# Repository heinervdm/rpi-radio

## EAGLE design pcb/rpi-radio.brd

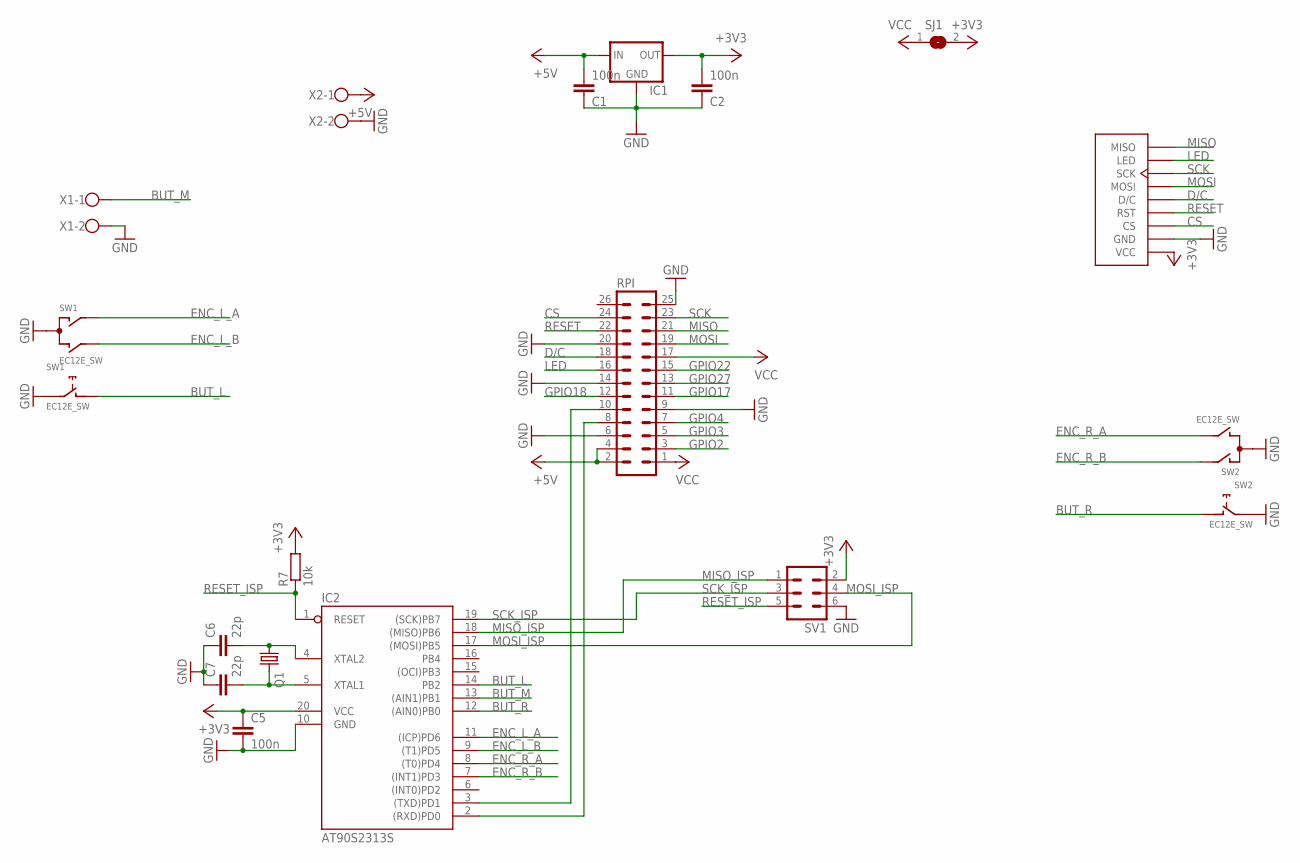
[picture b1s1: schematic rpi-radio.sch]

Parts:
C1, C2, C5: 100n; C0805
C6, C7: 22p; C0805
IC1: 78XXS
IC2: AT90S2313S; SO20L
Q1: CRYSTALHC49S; HC49/S
R7: 10k; M0805
RPI: ML26
SJ1: SJ
SV1: ML6
SW1, SW2: EC12E_SW; ALPS_EC12E_SW
U$4: DISPLAY
X1, X2: W237-102

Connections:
+3V3: C2.2, C5.1, IC1.OUT, IC2.20 (VCC), R7.2, SJ1.2, SV1.2, U$4.P$1 (VCC)
+5V: C1.2, IC1.IN, RPI.2, RPI.4, X2.1
BUT_L: IC2.14 (PB2), SW1.D (1)
BUT_M: IC2.13 ((AIN1)PB1), X1.1
BUT_R: IC2.12 ((AIN0)PB0), SW2.D (1)
CS: RPI.24, U$4.P$3 (CS)
D/C: RPI.18, U$4.P$5 (D/C)
ENC_L_A: IC2.11 ((ICP)PD6), SW1.A
ENC_L_B: IC2.9 ((T1)PD5), SW1.B
ENC_R_A: IC2.8 ((T0)PD4), SW2.B
ENC_R_B: IC2.7 ((INT1)PD3), SW2.A
GND: C1.1, C2.1, C5.2, C6.1, C7.1, IC1.GND, IC2.10 (GND), RPI.6, RPI.9, RPI.14, RPI.20, RPI.25, SV1.6, SW1.C, SW1.E (2), SW2.C, SW2.E (2), U$4.P$2 (GND), X1.2, X2.2
GPIO2: RPI.3
GPIO3: RPI.5
GPIO4: RPI.7
GPIO17: RPI.11
GPIO18: RPI.12
GPIO22: RPI.15
GPIO27: RPI.13
LED: RPI.16, U$4.P$8 (LED)
MISO: RPI.21, U$4.P$9 (MISO)
MISO_ISP: IC2.18 ((MISO)PB6), SV1.1
MOSI: RPI.19, U$4.P$6 (MOSI)
MOSI_ISP: IC2.17 ((MOSI)PB5), SV1.4
unnamed: C6.2, IC2.4 (XTAL2), Q1.1
unnamed: IC2.2 ((RXD)PD0), RPI.8
unnamed: IC2.3 ((TXD)PD1), RPI.10
unnamed: C7.2, IC2.5 (XTAL1), Q1.2
RESET: RPI.22, U$4.P$4 (RST)
RESET_ISP: IC2.1 (RESET), R7.1, SV1.5
SCK: RPI.23, U$4.P$7 (SCK)
SCK_ISP: IC2.19 ((SCK)PB7), SV1.3
VCC: RPI.1, RPI.17, SJ1.1

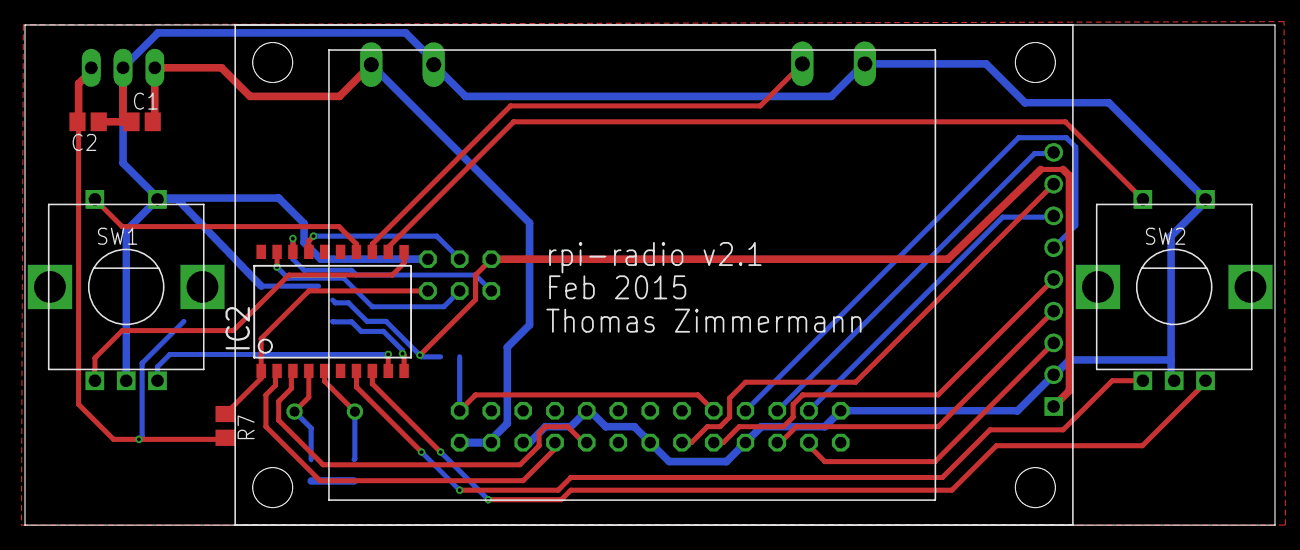
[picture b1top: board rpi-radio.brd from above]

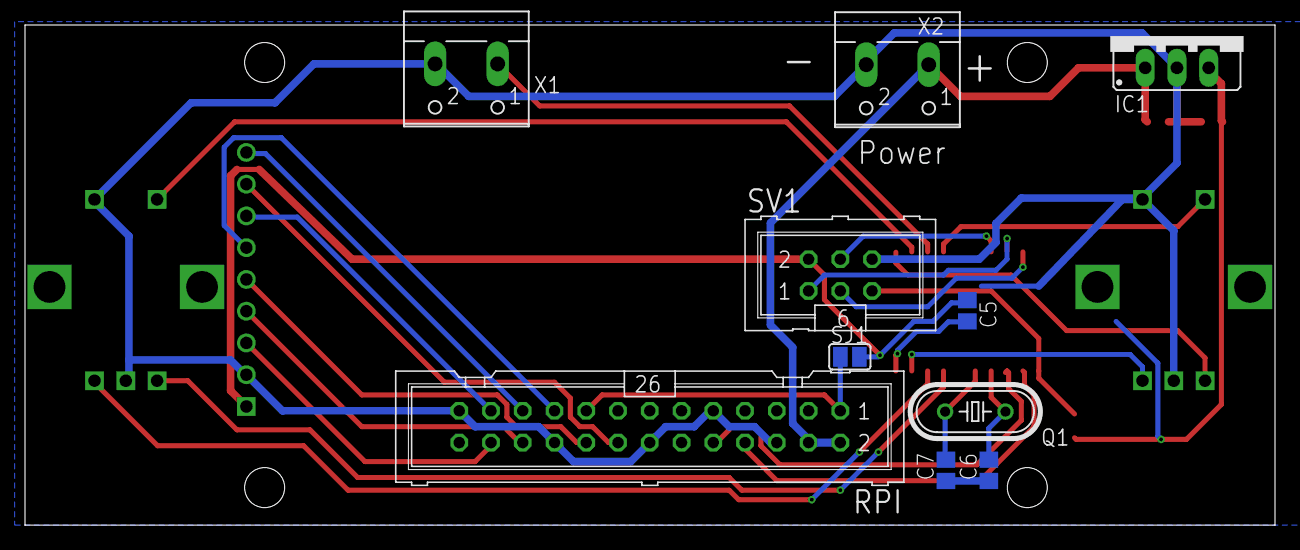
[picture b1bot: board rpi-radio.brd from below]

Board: 2 copper layers, 100.0 x 40.0 mm, 17 parts (10 on the bottom side), 26 nets.

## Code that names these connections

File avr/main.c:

/*
 * Debounce routine by Peter Dannegger: https://www.mikrocontroller.net/articles/Entprellung#Timer-Verfahren_.28nach_Peter_Dannegger.29
 * 
 * Rotary encoder routine by Peter Dannegger: https://www.mikrocontroller.net/articles/Drehgeber#Solide_L.C3.B6sung:_Beispielcode_in_C
 * 
 * UART lib by Peter Fleury: http://homepage.hispeed.ch/peterfleury/avr-software.html#libs
 */

#include <avr/interrupt.h>
#include <avr/io.h>
#include <stdlib.h>

#include "lib/uartlibrary/uart.h"

#ifndef F_CPU
#define F_CPU 14745600UL
#endif

#define UART_BAUD_RATE 9600

#define ENC_PIN    PIND
#define ENC_PORT   PORTD
#define ENC_DDR    DDRD
#define ENC0A_P    PD3
#define ENC0B_P    PD4
#define ENC1A_P    PD5
#define ENC1B_P    PD6

#define PHASE_0A     (ENC_PIN & 1<<ENC0A_P)
#define PHASE_0B     (ENC_PIN & 1<<ENC0B_P)
#define PHASE_1A     (ENC_PIN & 1<<ENC1A_P)
#define PHASE_1B     (ENC_PIN & 1<<ENC1B_P)

volatile int8_t enc_delta0, enc_delta1; // -128 ... 127
static int8_t last0, last1;

#define KEY_DDR         DDRB
#define KEY_PORT        PORTB
#define KEY_PIN         PINB
#define KEY0            0
#define KEY1            1
#define KEY2            2
#define ALL_KEYS        (1<<KEY0 | 1<<KEY1 | 1<<KEY2)
 
#define REPEAT_MASK     (1<<KEY1 | 1<<KEY2)       // repeat: key1, key2
#define REPEAT_START    250                       // after 250ms
#define REPEAT_NEXT     150                       // every 150ms
 
volatile uint8_t key_state;                                // debounced and inverted key state: bit = 1: key pressed
volatile uint8_t key_press;                                // key press detect
volatile uint8_t key_rpt;                                  // key long press and repeat

///////////////////////////////////////////////////////////////////
//
// check if a key has been pressed. Each pressed key is reported
// only once
//
uint8_t get_key_press( uint8_t key_mask ) {
	cli();                                          // read and clear atomic !
	key_mask &= key_press;                          // read key(s)
	key_press ^= key_mask;                          // clear key(s)
	sei();
	return key_mask;
}
 
///////////////////////////////////////////////////////////////////
//
// check if a key has been pressed long enough such that the
// key repeat functionality kicks in. After a small setup delay
// the key is reported being pressed in subsequent calls
// to this function. This simulates the user repeatedly
// pressing and releasing the key.
//
uint8_t get_key_rpt( uint8_t key_mask ) {
	cli();                                          // read and clear atomic !
	key_mask &= key_rpt;                            // read key(s)
	key_rpt ^= key_mask;                            // clear key(s)
	sei();
	return key_mask;
}
 
///////////////////////////////////////////////////////////////////
//
// check if a key is pressed right now
//
uint8_t get_key_state( uint8_t key_mask ) {
  key_mask &= key_state;
  return key_mask;
}
 
///////////////////////////////////////////////////////////////////
//
uint8_t get_key_short( uint8_t key_mask ) {
  cli();                                          // read key state and key press atomic !
  return get_key_press( ~key_state & key_mask );
}
 
///////////////////////////////////////////////////////////////////
//
uint8_t get_key_long( uint8_t key_mask ) {
  return get_key_press( get_key_rpt( key_mask ));
}


void encode_init( void ) {
	int8_t new;

	new = 0;
	if( PHASE_0A ) {
		new = 3;
	}
	if( PHASE_0B ) {
		new ^= 1;
	}
	last0 = new;

	new = 0;
	if( PHASE_1A ) {
		new = 3;
	}
	if( PHASE_1B ) {
		new ^= 1;                              // convert gray to binary
	}
	last1 = new;                               // power on state

	enc_delta0 = enc_delta1 = 0;
	TCCR0A = (1<<WGM01);                       // CTC
	TCCR0B = (1<<CS01)^(0<<CS00);              // XTAL / 8
	OCR0A = (uint8_t)(F_CPU / 128 / 1000 - 1); // set compare register
	TIMSK |= (1<<OCIE0A);                     // activate compare mode
}

int8_t encode_read0( void ) {        // read two step encoders
	int8_t val;

	cli();
	val = enc_delta0;
	enc_delta0 = val & 1;
	sei();
	return val >> 1;
}

int8_t encode_read1( void ) {        // read two step encoders
	int8_t val;

	cli();
	val = enc_delta1;
	enc_delta1 = val & 1;
	sei();
	return val >> 1;
}

int main(void) {
	int16_t c;
	int32_t enc_pos0, enc_pos1, last_enc_pos0, last_enc_pos1;
	char tc;
	char buf[12];

	uart_init( UART_BAUD_SELECT(UART_BAUD_RATE,F_CPU) );

	ENC_DDR  &= (0<<ENC0A_P) ^ (0<<ENC0B_P) ^ (0<<ENC1A_P) ^ (0<<ENC1B_P); // set ENC pin as input
	ENC_PORT |= (1<<ENC0A_P) ^ (1<<ENC0B_P) ^ (1<<ENC1A_P) ^ (1<<ENC1B_P); // enable internal pullups for ENC pin
	KEY_DDR &= ~ALL_KEYS;                // configure key port for input
	KEY_PORT |= ALL_KEYS;                // and turn on pull up resistors

	encode_init();
	sei();

	uart_puts("Info: Encoder reader started.\n");

	last_enc_pos0 = enc_pos0 = 0;
	last_enc_pos1 = enc_pos1 = 0;

	while (1) {
		c = uart_getc();
		if ( c & UART_NO_DATA ) {
		} else {
			if ( c & UART_FRAME_ERROR ) {
				uart_puts("Error: UART Framing\n");
			}
			if ( c & UART_OVERRUN_ERROR ) {
				uart_puts("Error: UART Overrun\n");
			}
			if ( c & UART_BUFFER_OVERFLOW ) {
				uart_puts("Error: Buffer Overflow\n");
			}
			tc = c & 0x00FF;
			switch (tc) {
				case '\r':
				case '\n':
				case '\0':
					break;
				case 's':
				case 'S':
					break;
				default:
					uart_puts("Error: Unknown command: ");
					uart_putc(tc);
					uart_putc('\n');
					break;
			}
		}
		enc_pos0 += encode_read0();
		if ( enc_pos0 != last_enc_pos0 ) {
			uart_puts("Encoder L: ");
			itoa( enc_pos0, buf, 10 );
			uart_puts(buf);
			uart_putc('\n');
			last_enc_pos0 = enc_pos0;
		}
		enc_pos1 += encode_read1();
		if ( enc_pos1 != last_enc_pos1 ) {
			uart_puts("Encoder R: ");
			itoa( enc_pos1, buf, 10 );
			uart_puts(buf);
			uart_putc('\n');
			last_enc_pos1 = enc_pos1;
		}
		if( get_key_press( 1<<KEY0 ) || get_key_rpt( 1<<KEY0 )) {
			uart_puts("Button Pressed: L\n");
		}
		if( get_key_press( 1<<KEY1 ) || get_key_rpt( 1<<KEY1 )) {
			uart_puts("Button Pressed: M\n");
		}
		if( get_key_press( 1<<KEY2 ) || get_key_rpt( 1<<KEY2 )) {
			uart_puts("Button Pressed: R\n");
		}
	}
	return 0;
}


ISR( TIMER0_COMPA_vect ) {              // poll encoder
	int8_t new, diff;

	new = 0;
	if( PHASE_0A ) {
		new = 3;
	}
	if( PHASE_0B ) {
		new ^= 1;                       // convert gray to binary
	}
	diff = last0 - new;                 // difference last - new
	if( diff & 1 ) {                    // bit 0 = value (1)
		last0 = new;                    // store new as next last
		enc_delta0 += (diff & 2) - 1;   // bit 1 = direction (+/-)
	}

	new = 0;
	if( PHASE_1A ) {
		new = 3;
	}
	if( PHASE_1B ) {
		new ^= 1;                       // convert gray to binary
	}
	diff = last1 - new;                 // difference last - new
	if( diff & 1) {                     // bit 0 = value (1)
		last1 = new;                    // store new as next last
		enc_delta1 += (diff & 2) - 1;   // bit 1 = direction (+/-)
	}

	static uint8_t ct0, ct1, rpt;
	uint8_t i;
	i = key_state ^ ~KEY_PIN;                       // key changed ?
	ct0 = ~( ct0 & i );                             // reset or count ct0
	ct1 = ct0 ^ (ct1 & i);                          // reset or count ct1
	i &= ct0 & ct1;                                 // count until roll over ?
	key_state ^= i;                                 // then toggle debounced state
	key_press |= key_state & i;                     // 0->1: key press detect
	
	if( (key_state & REPEAT_MASK) == 0) {            // check repeat function
		rpt = REPEAT_START;                          // start delay
	}
	if( --rpt == 0 ){
		rpt = REPEAT_NEXT;                            // repeat delay
		key_rpt |= key_state & REPEAT_MASK;
	}
}

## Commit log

2013-08-26 initial project import from KDevelop
2013-08-26 Add clock
2013-08-27 Move Clock in own widget and add player widget
2013-08-28 Add Station select dialog
2013-09-01 Add Volume widget
2013-09-15 Add QtSerialPort to cmake
2013-09-15 Read serial port
2014-02-09 fix small bug in grid layout of player widget
2014-02-12 Add GPIO class
2014-02-12 Add Encoder class
2014-02-12 Encoder: Add newPos signal
2014-02-12 Add csv file with stations extracted from chip.de
2014-02-12 Add qml for the player widget
2014-02-12 Add .gitignore
2014-02-13 Fix compilation errors in Encoder and GPIO classs
2014-02-13 Add cmake module for qtserialport lib
2014-02-13 remove qtserialport, the buttons will be read by the rpi directly
2014-02-13 Add Button class
2014-02-13 Fix some small errors
2014-02-13 Add License
2014-02-14 Correct button borders in player.qml
2014-02-14 Add class to handle controls
2014-02-14 Encoder: make parent QObject public
2014-02-14 install controls as eventfilter
2014-02-15 Use player.qml in PlayerWidget
2014-02-15 Add missing include
2014-02-15 use uint8_t for encoder values
2014-02-15 Use more then 8bit for encoder values
2014-02-15 Add debug output for controls
2014-02-16 Add clock.qml
2014-02-16 Use clock.qml
2014-02-16 Move include files to subdirectory
2014-02-16 Move qml Modules to qml subdir
2014-02-16 Move visibility handling of the diffent Widgets to qml
2014-02-16 Add StationList as qml and only use the QML modules, therefore delete the unused classes
2014-02-16 remove rpi-radio class, as this just wrapped PlayerWidget
2014-02-16 Move all cpp files except main.cpp into src and player.qml into qml
2014-02-16 Fix VolumeWidget
2014-02-16 Set right default volume
2014-02-16 Use states in qml
2014-02-17 Fix signal handling of Clock.qml
2014-02-17 Change states by Controls
2014-02-17 wip to register button click
2014-02-17 Make pushbuttons work
2014-02-17 Scale labels to width
2014-03-07 remove QApplication::GuiServer as this gives some kind of desktop
    And try to get fullscreen
2014-03-07 Make widget Fullscreen
2014-04-20 make playerwidget fullscreen and without borders
2014-05-11 Use GPIO pins from schematic
2014-05-14 resize to new display size
2014-05-14 Add PCB
2014-05-14 pcb: remove eagle.epf as it's not needed
2014-05-14 pcb: remove rpi-radio.pro, not needed
2014-05-18 use 1msec timer, because the encoder produces to short pulses
2014-05-19 Add AVR firmware to read the encoders and send them via uart
2014-05-19 avr: implement encoder and button routines
2014-05-19 pcb: add attiny2313, because rpi is not able to decode the rotary encoder and use thicker traces
2014-05-20 avr: correct values for repeated button press
2014-05-23 Add Qt5 support
2014-05-23 Use QSerialPort to read button and encoder data from serial port
2014-05-25 Start porting to qt5
2014-05-29 Fix qml's for qt5
2014-05-31 Use a CoverFlow widget for station list
2014-05-31 Try pushing stationlist from c++ to qml and try using qmultimedia
2014-06-01 make a controls qml widget
2014-06-01 Provide Stations from c++
2014-07-20 Go back to QtQuick 1
2014-07-24 Prepare CMakeLists to switch between Qt4 and Qt5
2014-07-25 Add back Qt4 support
2014-07-26 Fix playing sound with phonon
2014-08-06 Fix bug that name of the previous station is displayed in StationList.qml
2014-11-23 Update to version v2 of the pcb. the integrated amplifier did not work properly
2015-02-12 Fix wrong polarity of attiny
2015-10-04 Add PJ_RPI repo for GPIO functions
2015-10-08 Add qtmpdclient as submodule (Qt wrapper around libmpdclient)
2015-10-19 switch to my own qtmpdclient version
2015-10-19 correct path
2015-10-19 remove qtmpdclient submodule for now
2015-10-19 Readd my own QtMtpClient version as submodule
2015-10-19 Update to latest version
2015-10-20 Update CMakeLists
2015-10-20 Use PJ_RPI GPIO functions for Encoder
2016-07-12 Switch to mpd instead of Phonon
2016-07-12 Add missing MpdPlayerWidet.h, remove some unneded files
2016-07-16 Several updates
    - clean up CMakeList.txt, remove unused libs
    - Extend MenuList to highlight the currently played track in addition to the currently selected one.
    - Start Browse with mpd root instead of an additional layer
    - Add function to fetch the current playlist from mpd
    - When selecting a track or adding one to the playlist start to play this one
2016-07-17 MenuList.qml: split into List Playlist and Browse
    Split MenuList into a list and button part, so that one can use different buttons for the different lists.
2016-07-17 Add more icons from https://github.com/driftyco/ionicons
2016-07-17 MpdPlayerWidget: adjust to new menuList name
2016-07-24 insert playlist clear button
